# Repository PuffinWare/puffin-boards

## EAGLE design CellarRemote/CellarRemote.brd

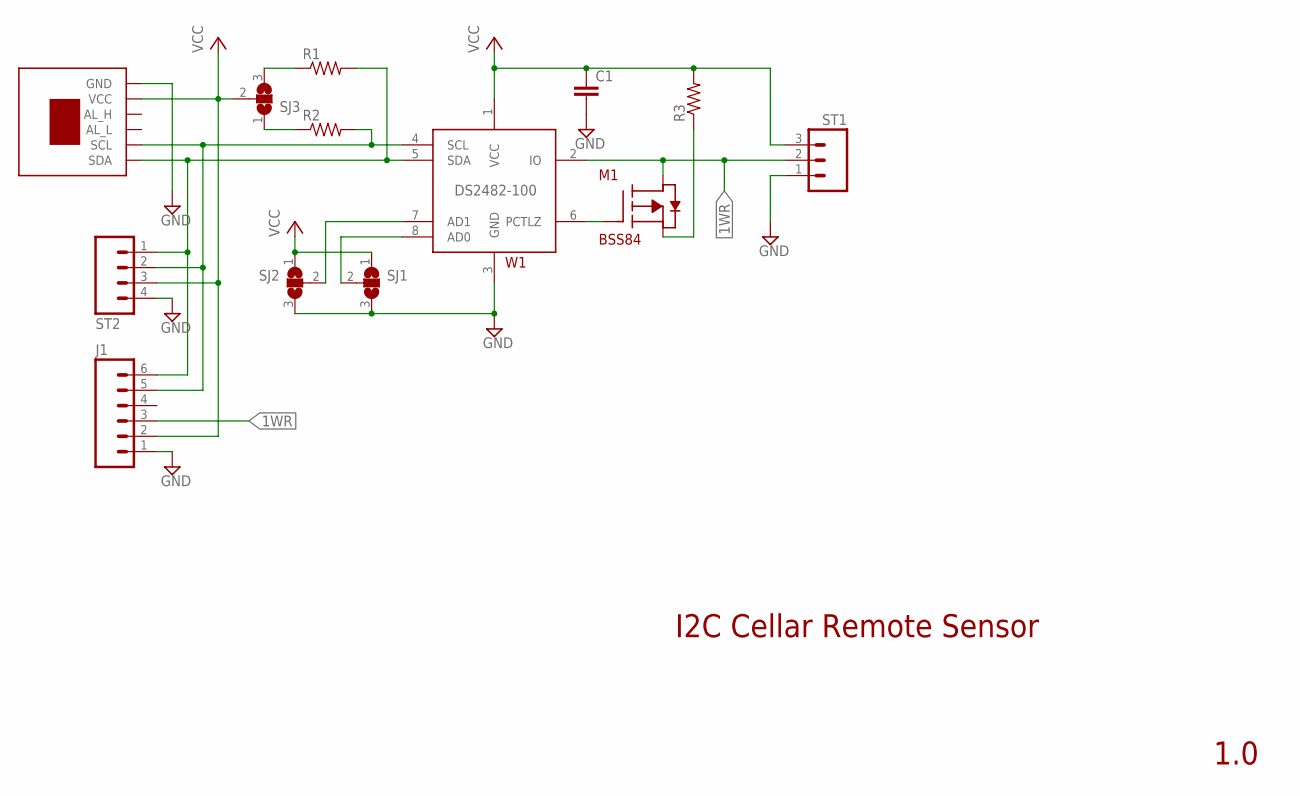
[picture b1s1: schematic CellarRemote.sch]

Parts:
C1: CAP0603-CAP; 0603-CAP
J1: M06SILK_FEMALE_PTH; 1X06
M1: BSS84; SOT-23
R1, R2: RESISTOR0603; 0603-RES
R3: RESISTORPTH-1/4W; AXIAL-0.4
SF_HIH: SPARKFUN_HIH6130
SJ1, SJ2, SJ3: SJ2W; SJ_2
ST1: SCREWTERM_3; SCREWTERM_0.2X3
ST2: SCREWTERM_4; SCREWTERM_0.2X4
W1: DS2482-100; SOIC8

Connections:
1WR: J1.3, M1.3, ST1.2, W1.2 (IO)
AD0: SJ1.2, W1.8 (AD0)
AD1: SJ2.2, W1.7 (AD1)
GND: C1.2, J1.1, SF_HIH.GND, SJ1.3, SJ2.3, ST1.1, ST2.4, W1.3 (GND)
unnamed: M1.1, W1.6 (PCTLZ)
unnamed: R1.1, SJ3.3
unnamed: R2.1, SJ3.1
unnamed: M1.2, R3.P$1 (1)
SCL: J1.5, R2.2, SF_HIH.SCL, ST2.2, W1.4 (SCL)
SDA: J1.6, R1.2, SF_HIH.SDA, ST2.1, W1.5 (SDA)
VCC: C1.1, J1.2, R3.P$2 (2), SF_HIH.VCC, SJ1.1, SJ2.1, SJ3.2, ST1.3, ST2.3, W1.1 (VCC)

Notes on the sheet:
1.0
I2C Cellar Remote Sensor

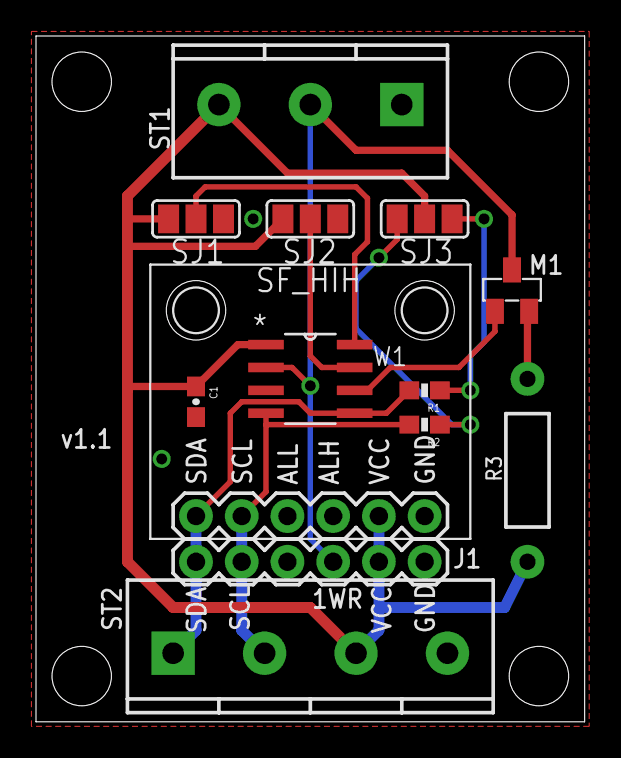
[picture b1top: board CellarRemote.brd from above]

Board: 2 copper layers, 30.5 x 38.1 mm, 19 parts (0 on the bottom side), 11 nets.

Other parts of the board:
U$1, U$2, U$3, U$4, U$6, U$7: STAND-OFF

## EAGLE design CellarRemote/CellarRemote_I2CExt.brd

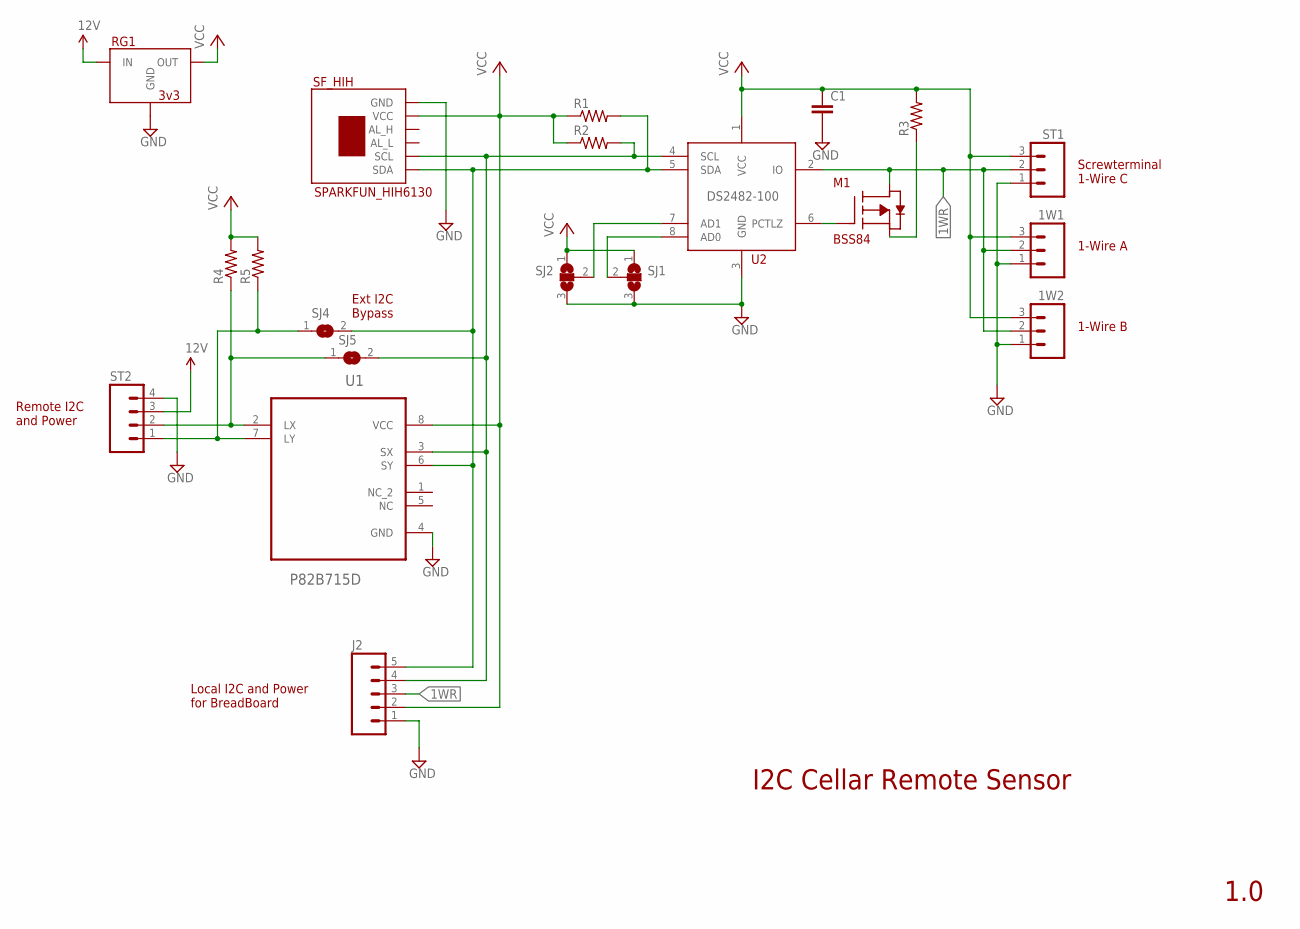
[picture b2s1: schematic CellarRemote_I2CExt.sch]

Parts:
1W1, 1W2: M03PTH; 1X03
C1: CAP0603-CAP; 0603-CAP
J2: M05PTH; 1X05
M1: BSS84; SOT-23
R1, R2: RESISTOR0603; 0603-RES
R3: RESISTORPTH-1/4W; AXIAL-0.4
R4, R5: RESISTOR0805-RES; 0805
RG1: 3v3; MURATA_REG_HOR
SF_HIH: SPARKFUN_HIH6130
SJ1, SJ2: SJ2W; SJ_2
SJ4, SJ5: SJ
ST1: SCREWTERM_3; SCREWTERM_0.2X3
ST2: SCREWTERM_4; SCREWTERM_0.2X4
U1: P82B715D; SOIC127P600X175-8N
U2: DS2482-100; SOIC8

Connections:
1WR: 1W1.2, 1W2.2, J2.3, M1.3, ST1.2, U2.2 (IO)
12V: RG1.1 (IN), ST2.3
AD0: SJ1.2, U2.8 (AD0)
AD1: SJ2.2, U2.7 (AD1)
GND: 1W1.1, 1W2.1, C1.2, J2.1, RG1.2 (GND), SF_HIH.GND, SJ1.3, SJ2.3, ST1.1, ST2.4, U1.4 (GND), U2.3 (GND)
unnamed: M1.1, U2.6 (PCTLZ)
unnamed: R4.1, SJ5.1, ST2.2, U1.2 (LX)
unnamed: R5.1, SJ4.1, ST2.1, U1.7 (LY)
unnamed: M1.2, R3.P$1 (1)
SCL: J2.4, R2.2, SF_HIH.SCL, SJ5.2, U1.3 (SX), U2.4 (SCL)
SDA: J2.5, R1.2, SF_HIH.SDA, SJ4.2, U1.6 (SY), U2.5 (SDA)
VCC: 1W1.3, 1W2.3, C1.1, J2.2, R1.1, R2.1, R3.P$2 (2), R4.2, R5.2, RG1.3 (OUT), SF_HIH.VCC, SJ1.1, SJ2.1, ST1.3, U1.8 (VCC), U2.1 (VCC)

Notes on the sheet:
1.0
I2C Cellar Remote Sensor
Remote I2C and Power
Local I2C and Power for BreadBoard
Screwterminal 1-Wire C
1-Wire A
1-Wire B
Ext I2C Bypass

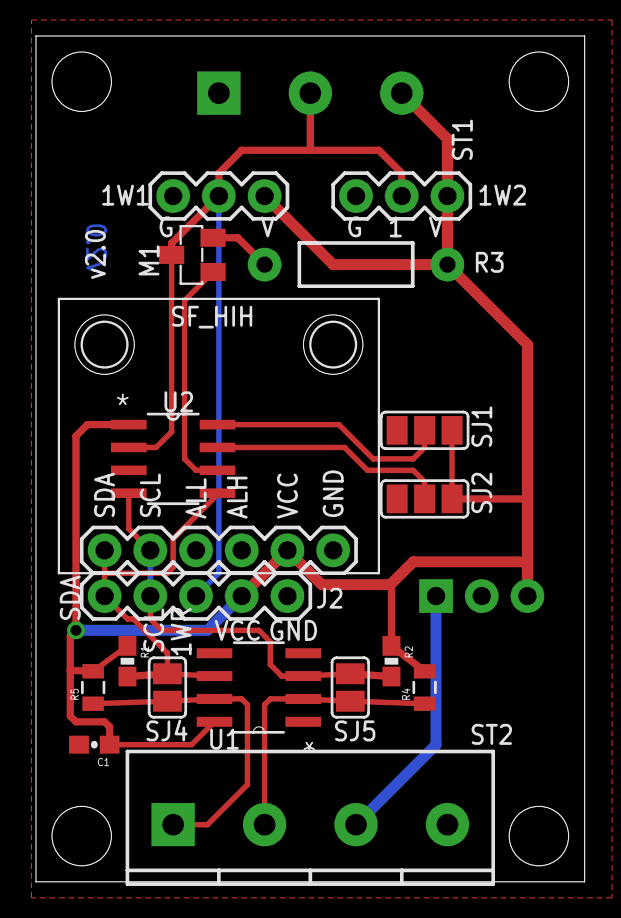
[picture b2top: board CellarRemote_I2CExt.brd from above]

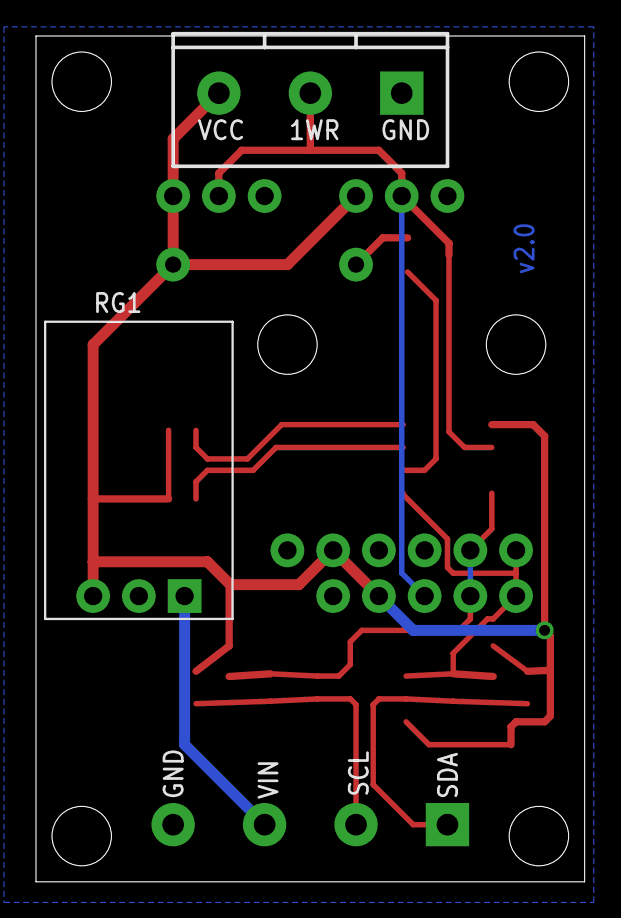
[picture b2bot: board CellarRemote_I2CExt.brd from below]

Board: 2 copper layers, 30.5 x 47.0 mm, 26 parts (2 on the bottom side), 12 nets.

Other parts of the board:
U$1, U$2, U$3, U$4, U$6, U$7: STAND-OFF

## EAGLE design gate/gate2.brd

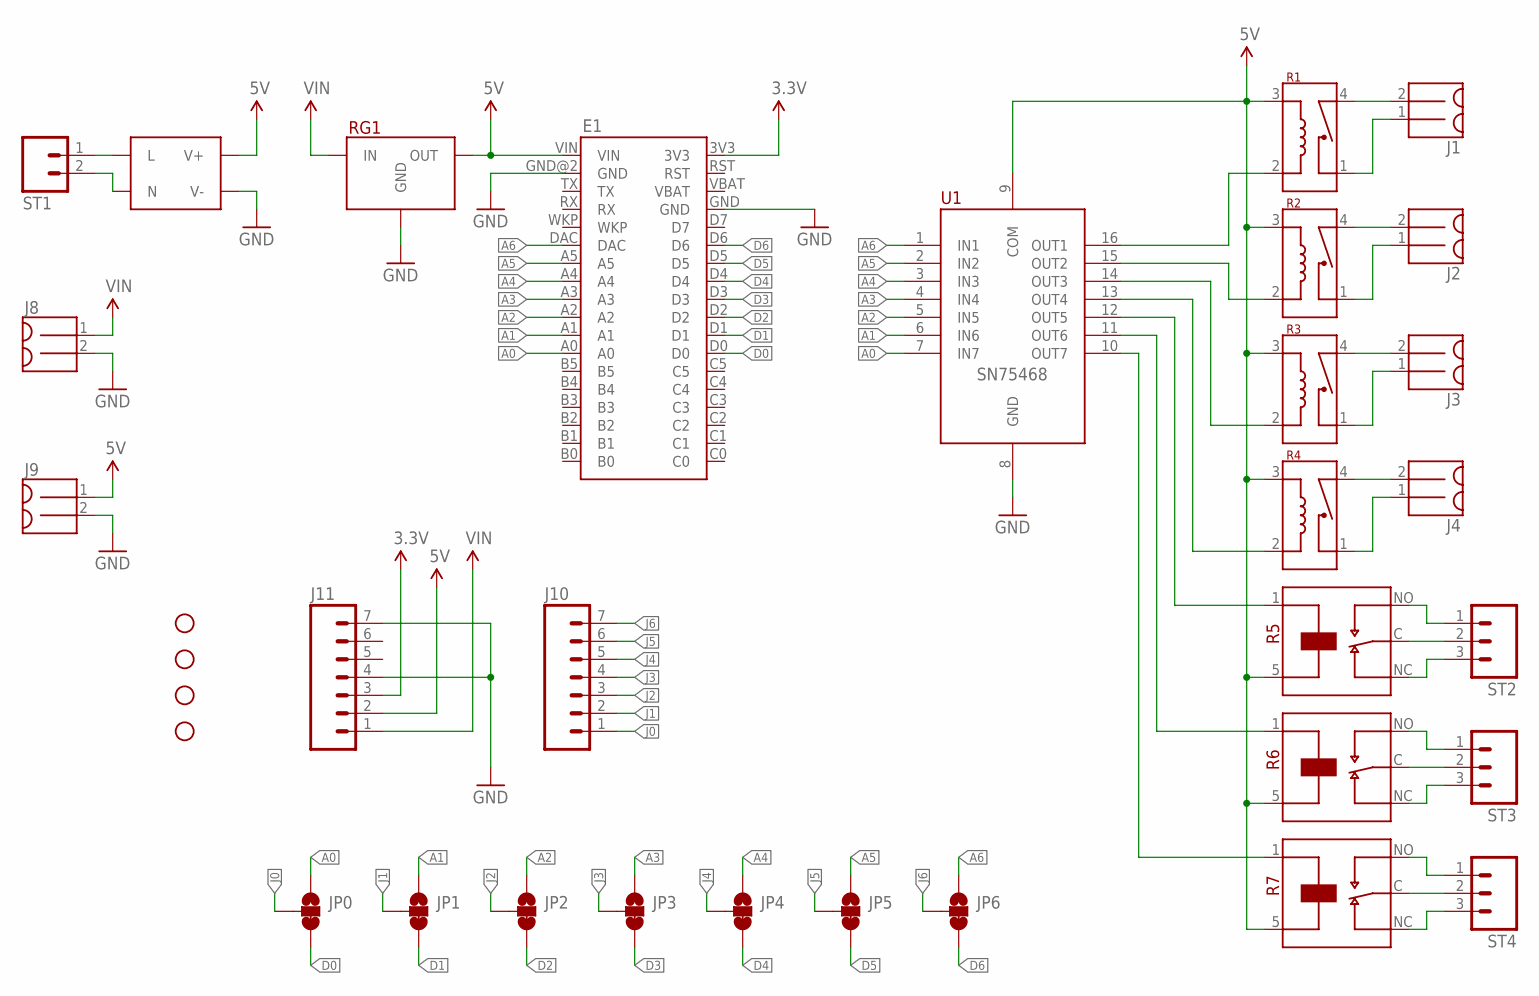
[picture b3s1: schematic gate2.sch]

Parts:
E1: ELECTRON
H1, H2, H3, H4: STAND-OFF
J1, J2, J3, J4, J8, J9: MOLEX_MINILITE_TRAP_2
J10, J11: M07; 1X07
JP0, JP1, JP2, JP3, JP4, JP5, JP6: JUMPER-PAD-3-2OF3_NC_BY_TRACE_SMALL; PAD-JUMPER-3-2OF3_NC_BY_TRACE_YES_SILK_FULL_BOX
PS1: IRM_03_PS_3W
R1, R2, R3, R4: HE3600_RELAY
R5, R6, R7: G2RL_SPDT
RG1: MURATA_REG; MURATA_REG_HOR
ST1: SCREWTERM_2; SCREWTERM_0.2X2
ST2, ST3, ST4: SCREWTERM_3; SCREWTERM_0.2X3
U1: SN75468; SOIC16

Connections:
3.3V: E1.3V3, J11.3
5V: E1.VIN, J9.1, J11.2, PS1.V+, R1.3 (R2), R2.3 (R2), R3.3 (R2), R4.3 (R2), R5.5, R6.5, R7.5, RG1.3 (OUT), U1.9 (COM)
A0: E1.A0, JP0.1, U1.7 (IN7)
A1: E1.A1, JP1.1, U1.6 (IN6)
A2: E1.A2, JP2.1, U1.5 (IN5)
A3: E1.A3, JP3.1, U1.4 (IN4)
A4: E1.A4, JP4.1, U1.3 (IN3)
A5: E1.A5, JP5.1, U1.2 (IN2)
A6: E1.DAC, JP6.1, U1.1 (IN1)
D0: E1.D0, JP0.3
D1: E1.D1, JP1.3
D2: E1.D2, JP2.3
D3: E1.D3, JP3.3
D4: E1.D4, JP4.3
D5: E1.D5, JP5.3
D6: E1.D6, JP6.3
GND: E1.GND, E1.GND@2 (GND), J8.2, J9.2, J11.4, J11.7, PS1.V-, RG1.2 (GND), U1.8 (GND)
J0: J10.1, JP0.2
J1: J10.2, JP1.2
J2: J10.3, JP2.2
J3: J10.4, JP3.2
J4: J10.5, JP4.2
J5: J10.6, JP5.2
J6: J10.7, JP6.2
unnamed: PS1.ACL (L), ST1.1
unnamed: R1.2 (R1), U1.16 (OUT1)
unnamed: R2.2 (R1), U1.15 (OUT2)
unnamed: R3.2 (R1), U1.14 (OUT3)
unnamed: R4.2 (R1), U1.13 (OUT4)
unnamed: J1.2, R1.4 (C2)
unnamed: J2.2, R2.4 (C2)
unnamed: J3.2, R3.4 (C2)
unnamed: J3.1, R3.1 (C1)
unnamed: J2.1, R2.1 (C1)
unnamed: J1.1, R1.1 (C1)
unnamed: J4.2, R4.4 (C2)
unnamed: J4.1, R4.1 (C1)
unnamed: R5.C, ST2.2
unnamed: R6.C, ST3.2
unnamed: R7.C, ST4.2
unnamed: R5.NO, ST2.1
unnamed: R5.NC, ST2.3
unnamed: R6.NO, ST3.1
unnamed: R6.NC, ST3.3
unnamed: R7.NO, ST4.1
unnamed: R7.NC, ST4.3
unnamed: PS1.ACN (N), ST1.2
unnamed: R5.1, U1.12 (OUT5)
unnamed: R6.1, U1.11 (OUT6)
unnamed: R7.1, U1.10 (OUT7)
VIN: J8.1, J11.1, RG1.1 (IN)

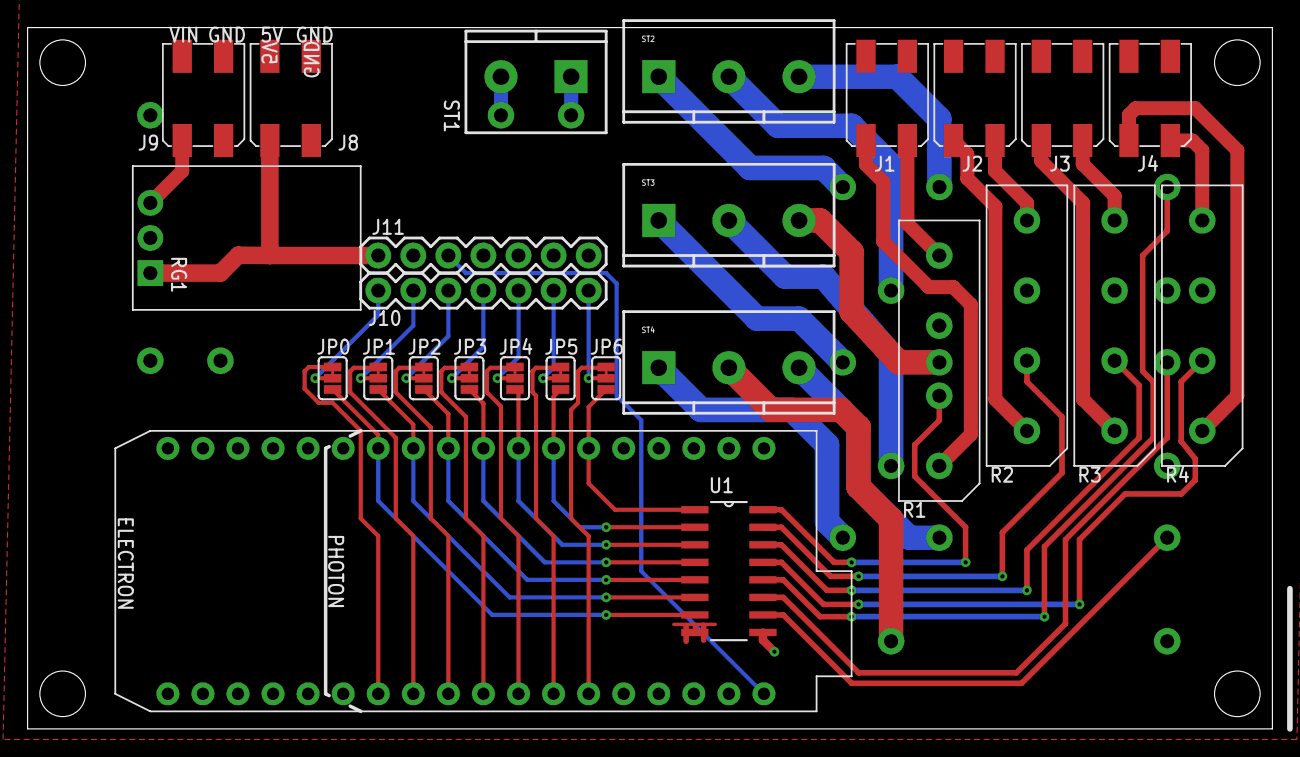
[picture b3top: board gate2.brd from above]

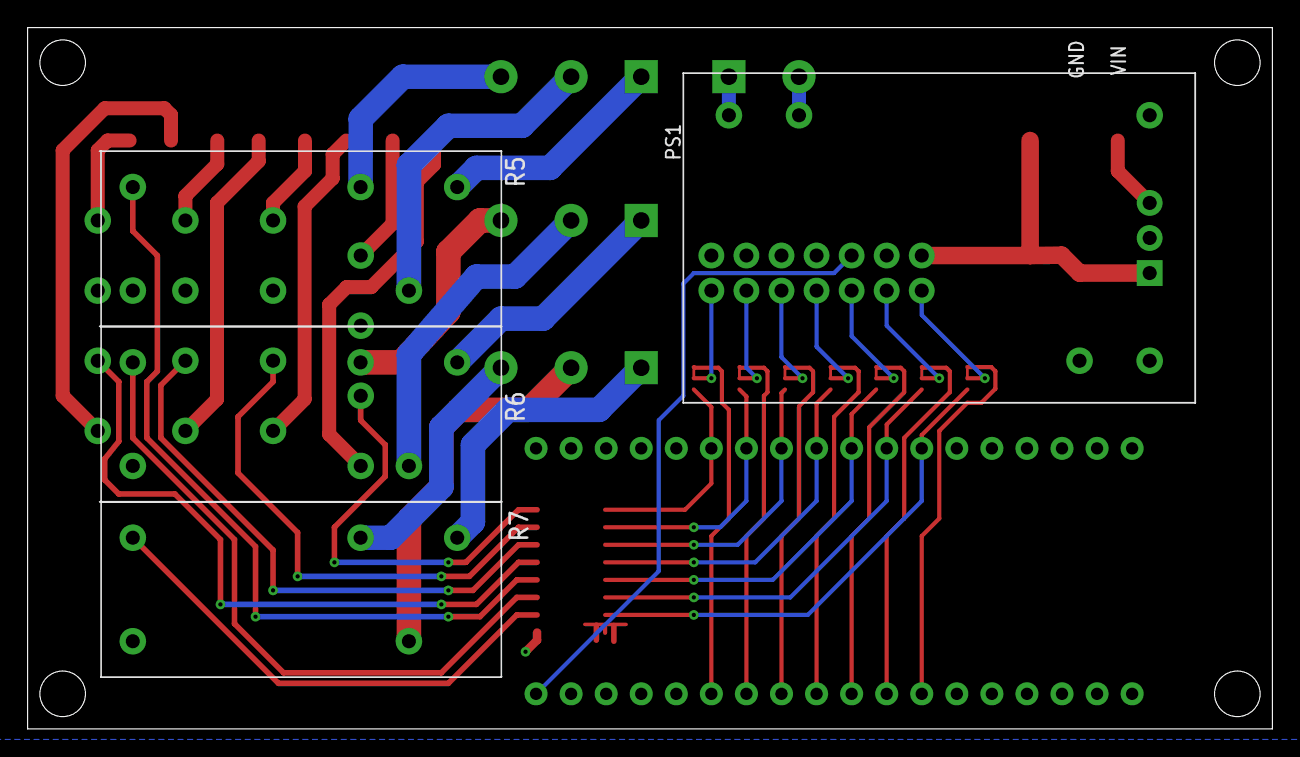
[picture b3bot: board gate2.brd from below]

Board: 2 copper layers, 90.2 x 50.8 mm, 34 parts (4 on the bottom side), 51 nets.

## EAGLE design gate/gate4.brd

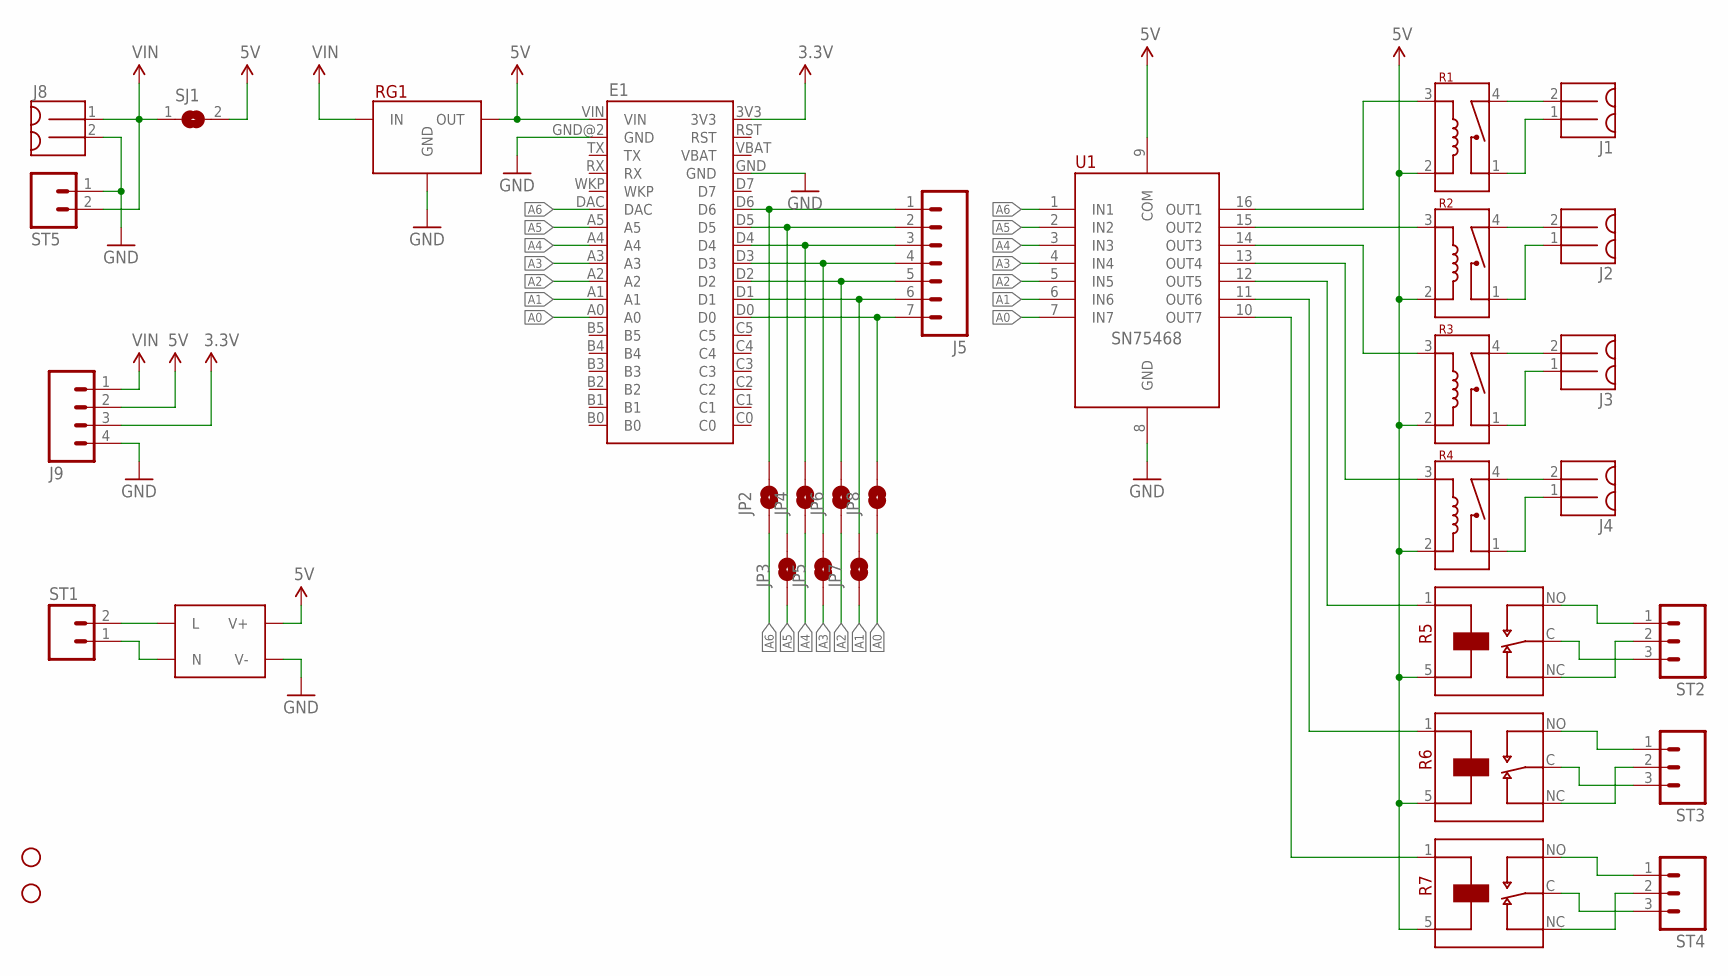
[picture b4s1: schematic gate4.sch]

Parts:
E1: ELECTRON
H1, H2: STAND-OFF
J1, J2, J3, J4, J8: MOLEX_MINILITE_TRAP_2
J5: M07; 1X07
J9: M04PTH; 1X04
JP2, JP3, JP4, JP5, JP6, JP7, JP8: JUMPER-PAD-2-NOYES_SILK; PAD-JUMPER-2-NO_YES_SILK
PS1: IRM_03_PS_3W
R1, R2, R3, R4: HE3600_RELAY
R5, R6, R7: G2RL_SPDT
RG1: MURATA_REG; MURATA_REG_HOR
SJ1: SJ
ST1, ST5: SCREWTERM_2; SCREWTERM_0.2X2
ST2, ST3, ST4: SCREWTERM_3; SCREWTERM_0.2X3
U1: SN75468; SOIC16

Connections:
3.3V: E1.3V3, J9.3
5V: E1.VIN, J9.2, PS1.V+, R1.2 (R1), R2.2 (R1), R3.2 (R1), R4.2 (R1), R5.5, R6.5, R7.5, RG1.3 (OUT), SJ1.2, U1.9 (COM)
A0: E1.A0, JP8.1, U1.7 (IN7)
A1: E1.A1, JP7.1, U1.6 (IN6)
A2: E1.A2, JP6.1, U1.5 (IN5)
A3: E1.A3, JP5.1, U1.4 (IN4)
A4: E1.A4, JP4.1, U1.3 (IN3)
A5: E1.A5, JP3.1, U1.2 (IN2)
A6: E1.DAC, JP2.1, U1.1 (IN1)
GND: E1.GND, E1.GND@2 (GND), J8.2, J9.4, PS1.V-, RG1.2 (GND), ST5.1, U1.8 (GND)
unnamed: PS1.ACL (L), ST1.2
unnamed: R4.3 (R2), U1.13 (OUT4)
unnamed: R5.1, U1.12 (OUT5)
unnamed: R6.1, U1.11 (OUT6)
unnamed: R7.1, U1.10 (OUT7)
unnamed: J4.2, R4.4 (C2)
unnamed: J3.2, R3.4 (C2)
unnamed: J2.2, R2.4 (C2)
unnamed: J2.1, R2.1 (C1)
unnamed: J3.1, R3.1 (C1)
unnamed: J4.1, R4.1 (C1)
unnamed: J1.2, R1.4 (C2)
unnamed: J1.1, R1.1 (C1)
unnamed: R6.NO, ST3.1
unnamed: R6.NC, ST3.2
unnamed: R5.NO, ST2.1
unnamed: R5.C, ST2.3
unnamed: R6.C, ST3.3
unnamed: R7.NC, ST4.2
unnamed: R7.C, ST4.3
unnamed: R5.NC, ST2.2
unnamed: R2.3 (R2), U1.15 (OUT2)
unnamed: PS1.ACN (N), ST1.1
unnamed: R7.NO, ST4.1
unnamed: E1.D0, J5.7, JP8.2
unnamed: E1.D1, J5.6, JP7.2
unnamed: E1.D2, J5.5, JP6.2
unnamed: R1.3 (R2), U1.16 (OUT1)
unnamed: E1.D3, J5.4, JP5.2
unnamed: R3.3 (R2), U1.14 (OUT3)
unnamed: E1.D4, J5.3, JP4.2
unnamed: E1.D5, J5.2, JP3.2
unnamed: E1.D6, J5.1, JP2.2
VIN: J8.1, J9.1, RG1.1 (IN), SJ1.1, ST5.2

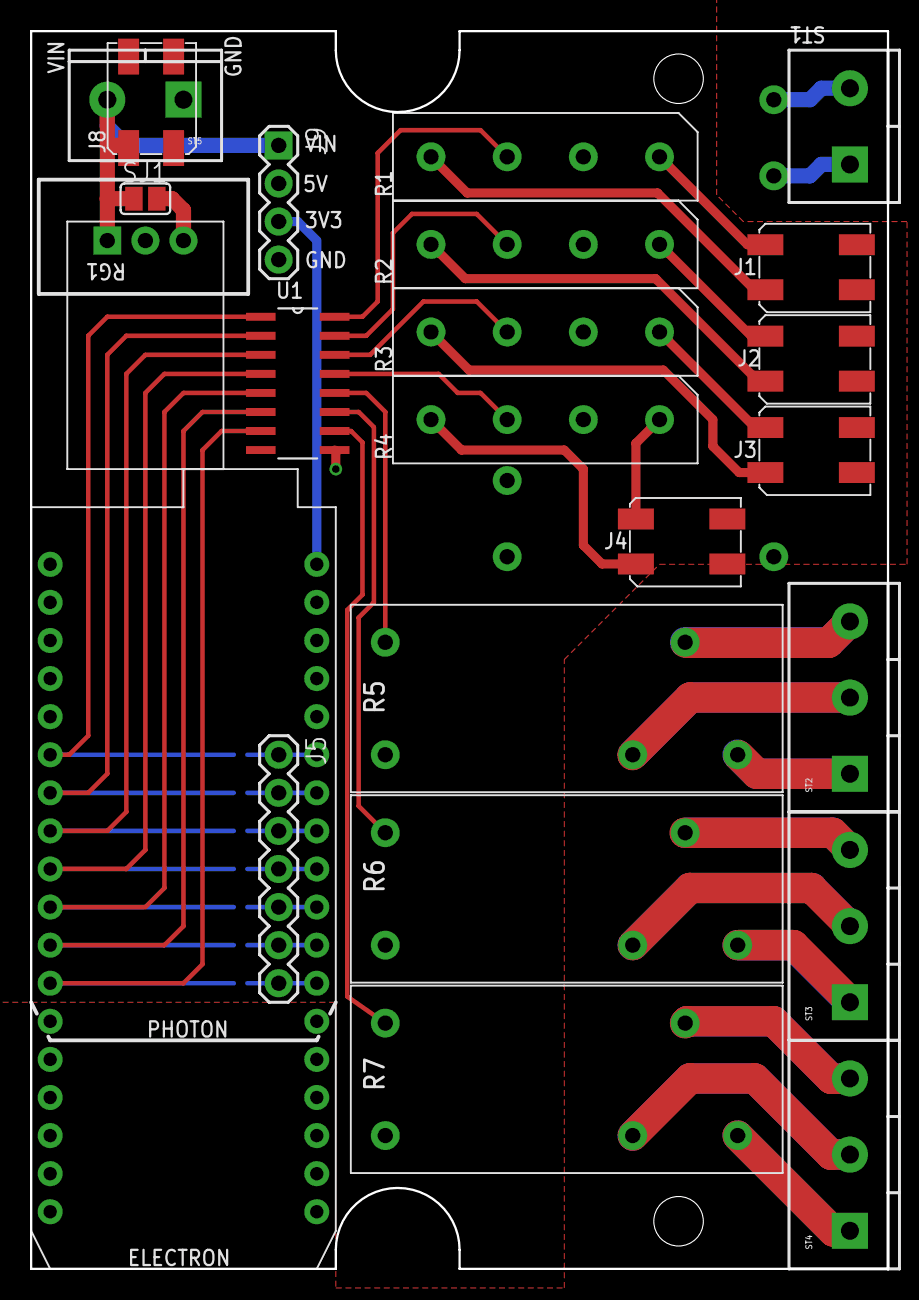
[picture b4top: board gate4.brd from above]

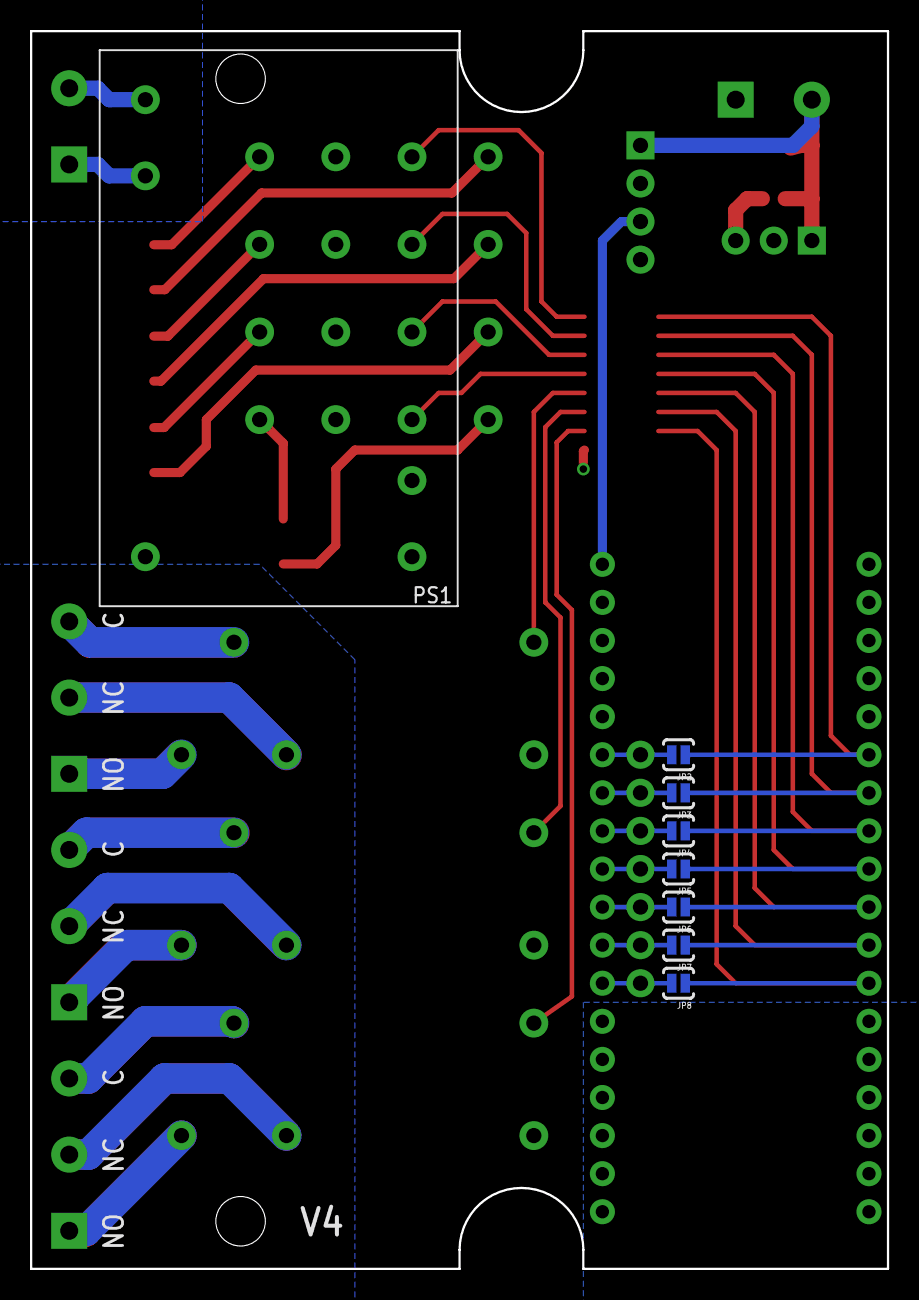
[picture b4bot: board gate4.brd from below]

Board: 2 copper layers, 57.1 x 82.5 mm, 33 parts (8 on the bottom side), 44 nets.

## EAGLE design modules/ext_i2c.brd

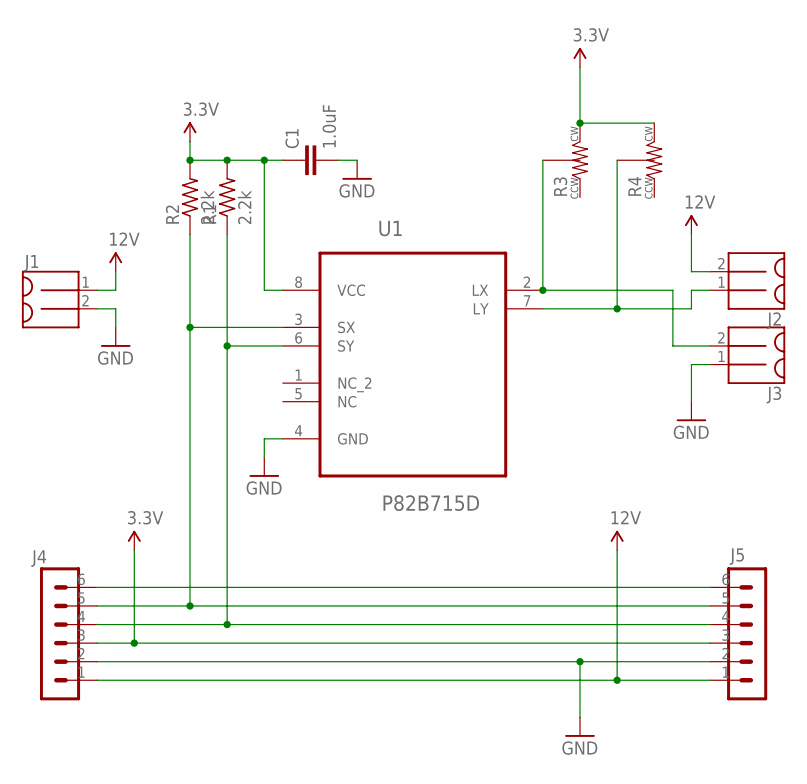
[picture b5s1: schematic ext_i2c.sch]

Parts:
C1: 1.0uF; 0603-CAP
J1, J2, J3: MOLEX_MINILITE_TRAP_2
J4: 1X06_HEADER_L1X06_EDGE_L; 1X06_EDGE_L
J5: 1X06_HEADER_R1X06_EDGE_R; 1X06_EDGE_R
R1, R2: 2.2k; R0805
R3, R4: POT_3MM
U1: P82B715D; SOIC127P600X175-8N

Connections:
3.3V: C1.1, J4.3, J5.3, R1.2, R2.2, R3.3, R4.3, U1.8 (VCC)
12V: J1.1, J2.2, J4.1, J5.1
GND: C1.2, J1.2, J3.1, J4.2, J5.2, U1.4 (GND)
unnamed: J4.6, J5.6
unnamed: J4.5, J5.5, R2.1, U1.3 (SX)
unnamed: J4.4, J5.4, R1.1, U1.6 (SY)
unnamed: J3.2, R3.2, U1.2 (LX)
unnamed: J2.1, R4.2, U1.7 (LY)

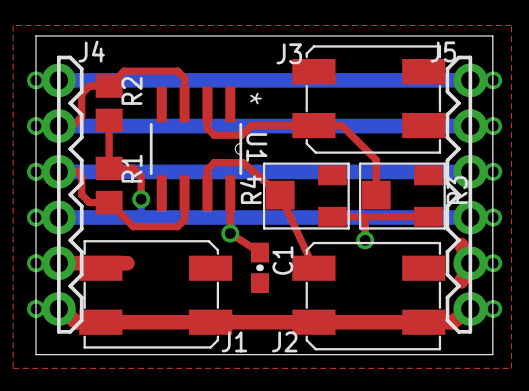
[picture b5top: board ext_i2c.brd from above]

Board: 2 copper layers, 25.4 x 17.7 mm, 11 parts (0 on the bottom side), 8 nets.

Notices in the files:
parts and their libraries:
SparkFun-Capacitors: Licensing: Creative Commons ShareAlike 4.0 International - https://creativecommons.org/licenses/by-sa/4.0
